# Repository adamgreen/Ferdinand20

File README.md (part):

<br>
Tracking the build of my robot to compete in the
[Seattle Robotics Society's Robo-Magellan](https://robothon.org/rules-robo-magellan/) competition that was to be held on October 3rd, 2020 at the Seattle Center but is now cancelled due to COVID-19. Development of this robot will continue in hopes that it can compete in the future.

## Points of Interest
[SRS Robo-Magellan rules](https://robothon.org/rules-robo-magellan/) <br>
[Notes about our 2014 bot](https://github.com/adamgreen/Ferdinand14#readme) <br>
[Notes from my stalled 2016 attempt](https://github.com/adamgreen/Ferdinand16#readme) <br>
[How to Clone GitHub Repository](#clone-this-repo-and-its-submodules) <br>
[Sawppy the Rover Build Instructions](https://github.com/Roger-random/Sawppy_Rover#readme) <br>

---
## June 27th, 2021
### I2C? What I2C?
The next task I set myself upon was wiring the IMU into the LPC1768 on my Sawppy bot so that I could use it with the [dead reckoning code that I wrote for the Ferdinand16 project](https://github.com/adamgreen/Ferdinand16/tree/master/firmware/robot). When I was working with the IMU hardware back in April, I had it connected to a dedicated LPC1768 on a breadboard and not the one already wired up to my bot. When I went to move it over to the LPC1768 microcontroller on the Sawppy bot, I hit a snag. All of the I2C capable pins on the microcontroller were already being used for their UART functionality: LX-16A servos/motors, MRI debug monitor, and PDB communication.

### Bridge It
In the future, I plan to create my own PCB for the LPC1768 based brains of my bot which will give me access to more pins of the microcontroller. In the meantime, I would like to continue prototyping with the mbed based board that I already have. How can I work around the lack of free I2C pins? It turns out that I still have one set of SPI pins available. Using another microcontroller, I could create a bridge device that reads the IMU sensors via I2C and then sends the resulting readings to my main microcontroller over SPI.

#### LPC1768 as SPI Slave
My first attempt at building this bridge was to use another mbed LPC1768 microcontroller as a SPI slave. When I originally skimmed the mbed SPISlave class documentation I was kind of confused on how to really use it. I then read the LPC1768 User Manual and was even more confused. I tried for several days to get the LPC1768 to reliably send data back to the SPI master but ended up throwing in the towel. I just don't think the SPI peripheral on the LPC1768 hardware is designed properly for use in slave mode:
* There is no way to get an interrupt when the master sends a single byte request. It will only interrupt when the Rx buffer overflows, the Rx FIFO is half full, or 4 byte times have elapsed since the last received byte.
* It is really hard to queue up the Tx data at the right time and if you don't have it queued in time because your code is busy doing something else, the peripheral just takes the oldest already sent data from the Tx buffer and sends it instead.

In the end, I gave up on the LPC1768 and decided to research using another microcontroller from my stash.

#### nRF5x as SPI Slave
I had an [Adafruit Feather nRF52 Pro with myNewt Bootloader - nRF52832](https://www.adafruit.com/product/3574) in my stash of development boards so I pulled up its SPI slave documentation. What I saw there looked very promising:
* You can specify what data should be returned when you have no active data queued up to be sent back.
* Once you do have data to be sent, you queue it all up at once with the help of EasyDMA.

I ported my I2C sensor reading code to the nRF52832 and quickly implemented the SPI bridging code. The SPI Slave functionality on this device worked exactly as expected and I soon had a functional bridge setup between the bot's main LPC1768 and the nRF52 bridge.

Now to get it all installed back on my bot and start writing some dead reckoning code :)

---
## June 4th, 2021
### LX-16A Encoders
 <br>

The [LX-16A servos](https://www.hiwonder.hk/collections/servo/products/hiwonder-lx-16a-serial-bus-servo) used in the [Sawppy Rover](https://github.com/Roger-random/Sawppy_Rover#readme) design have a potentiometer that can be used for reading out the current angle but it can't accurately read all 360 degrees of the rotation. It returns accurate readings between -40 and 280 degrees (320 degrees of rotation) but not such accurate readings for the other 40 degrees of rotation. There are 2 types of inaccurate readings that it returns when in the range between 280 and -40 degrees (the deadzone):
* It will return angle values that fall between 280 and -40 as expected but they aren't accurate. This is the most common case and is easy for me to detect in code. I suspect that there is a carbon arc for the section where it returns correct values (-40 to 280 degrees) and maybe just copper at the two extremes where it returns these incorrect readings. The following diagrams show what I think the internals of the potentiometer look like and where the wiper is located for a few key angles:
  * 280 degrees: This is the maximum valid angle. The potentiometer wiper is contacting the carbon resistive track. <br>
  * -40 degrees: This is the minimum valid angle and shows the potentiometer wiper at the other end of the carbon resistive track. <br> 
  * -50 degrees: This is an angle in the deadzone. The potentiometer is no longer on the carbon resistive track but is also not floating. This explains why the readings back from the LX-16A servo tend to fall around -40 or 280 when in the deadzone since this area of the track is at either the maximum or minimum voltage level since there is so little resistance to the end taps. <br> 
* It will return random angle readings that can fall anywhere in the 360 degree range. I suspect that this happens when the potentiometer wiper is left floating in a gap that must exist between the two ends of the potentiometer to stop the wiper from creating a short between the high and low voltages applied to the opposite ends of the potentiometer. This isn't a common case and is hard to detect in code but we do know that it happens when previous readings place it in the deadzone and the wiper shouldn't dwell in this area for long at the velocities and sampling times that will be used for controlling my robot's motion. <br> 

I tried two methods to work around these inaccurate readings and I will give an overview of them below.

#### Kalman Approach
 <br>
As the old saying goes, "When all you have is a hammer, everything looks like a nail." In my case, my hammer of choice has become the Kalman filter. So my first thought to solve the LX-16A servo encoder problem was to apply a Kalman filter to calculate the current rotational position and velocity. To this end, I started out by re-reading my ["Kalman Filter for Beginners with MATLAB Examples" by Phil Kim](https://www.amazon.com/Kalman-Filter-Beginners-MATLAB-Examples/dp/1463648359). I really like this book. The content is very good. The only down point is the Korean to English translation could use quite a bit of improvement. Once I finished the reread, I wrote up some code to experiment with the Kalman filter which can be seen in the following [commit](https://github.com/adamgreen/Ferdinand20/commit/b95c3b9d9873d6a039cecfaa98e94790804dd103). I played with this code for a few days but I never got the error estimates to a point where the rotational velocity estimate wasn't overly filtered with a lagging response to real world velocity changes. Based on these results, I decided to try another approach which can be best described as a bunch of conditional hacks.

#### Conditional Hacks
The key observation that I take advantage of in my set of hacks is the following:
* If the angle returned from the LX-16A servo is between -40 and 280 degrees, then most likely it is within +/-0.24 degrees (1 lsb) of the actual real world position.

This means that my code treats such position measurements as the truth and uses them to estimate the velocity. There is one exception to this and I will discuss it more later.

The second observation is very much related to that first one:
* If the angle returned from the LX-16A servo is instead between 280 degrees and -40 degrees then it is in a deadzone where the returned values are much less accurate.

When my code detects that the returned position readings are in this deadzone, it uses the previous position and velocity estimates and sampling time to calculate new position estimates by assuming constant velocity between the samples.

The handling of those two angle ranges gets us most of the way to a solution but I needed to add a few more conditional hacks to produce a functional filter:
* When the wiper is in the middle of the deadzone, it will be floating and returning completely random values that fall in or outside of the deadzone. I have the code ignore the first non-deadzone sample when the previous sample was from the deadzone. If this ignored non-deadzone angle is followed by another then the code transitions into the non-deadzone logic previously described. This does mean that the first good angle reading is always dropped when transitioning out of the deadzone but that is a small price to pay for filtering out these completely erroneous readings. I only expect a single erroneous reading caused by a floating wiper when the rover is moving since there should be a very low likelihood that the wiper stays in this region for multiple samples as the motor is rotating.
* Don't update the velocity until it has two or more non-deadzone position readings. The last interpolated position from the deadzone logic might be so incorrect that it would result in a very bad estimate of the velocity.
* Use an exponential recursive moving average filter to smooth out the velocity calculations. We don't want high frequency noise in this calculation to later impact the PID control loop.

```c++
void LX16A_DriveMotor::updateState()
{
    // Calculate time since last running of the filter and grab the current servo position in close temporal
    // relation to the time capture.
    int16_t servoPos = m_servo.getPosition();
    uint32_t currSampleTime = m_timer.read_us();
    uint32_t elapsedMicroSec = currSampleTime - m_lastSampleTime;
    m_lastSampleTime = currSampleTime;
    float dt = (float)elapsedMicroSec / 1000000.0f;

    EncoderState prevState = m_currState;
    if (ignoringNonDeadZoneSamples(servoPos) || isServoInDeadZone(servoPos))
    {
        // The servo position could be off by as much as +/-20 degrees when in dead zone of the pot.
        // Assume that the motor is still spinning at the same rate when in dead zone.
        m_currState.angle = constrainAngle(prevState.angle + prevState.velocity * dt);
        m_currState.velocity = prevState.velocity;
        m_wasInDeadZone = true;
        printf("*");
    }
    else
    {
        // The pot reading should be accurate so use it.
        m_currState.angle = constrainAngle(servoPos * LX16A_SERVO_TO_RADIAN_VALUE);

        if (m_wasInDeadZone)
        {
            // Don't want to base current velocity off of previously interpolated position.
            m_currState.velocity = prevState.velocity;
        }
        else
        {
            // Calculate velocity from change in angle and then use weighted average so that it doesn't snap too much.
            const float weight = VELOCITY_AVERAGING_WEIGHT;
            float angleDelta = constrainAngle(fmodf(m_currState.angle - prevState.angle, 2.0f*(float)M_PI));
            float velocity = angleDelta / dt;
            m_currState.velocity = (1.0f-weight)*m_currState.velocity + weight*velocity;
        }
        m_wasInDeadZone = false;
    }

    updatePID(dt);
}
```

I may have to add code in the future to handle the motor being stopped when in the deadzone or even worse, stopped right at the point where the potentiometer wiper is left floating. I will cross this bridge once I encounter it so that I have scenarios to use for testing my attempts to resolve it.

### Closing the Loop
Once I had a way to obtain a reasonably reliable estimate of the servo's rotational velocity, I pulled over my PID code from my old [Ferdinand16 repository](https://github.com/adamgreen/Ferdinand16#readme). The biggest changes I made to this code after copying include:
* Now allowing the sample time to be changed between PID updates as the frequency of the LX-16A servo position reads may not be as consistent as my previous uses of the PID control algorithm.
* Ferdinand16 required the angle error to be normalized between +/- 180 degrees and the PID code had this hardcoded into it. I updated the code to take an optional callback for performing such normalizations when required. It isn't required for LX-16A motor velocity control.

Now that I had a way to close the loop on the control of the motor velocities, I went into the existing ```SawppyDrive``` class and plugged in my new ```LX16A_DriveMotor``` class for controlling the 6 servos that spin the wheels (while leaving the 4 turning servos as is). Once this switch had been made, I could drive my Sawppy bot around by remote control as before but now the wheel velocities were running under closed loop control.

### MRIPROG / BLEMRI Issues with new macOS and MRI Updates
When I started testing the new PID code on my actual Sawppy based robot, I hit a few issues with my Bluetooth Low Energy (BLE) programming/debugging tools that I had to address first. It turns out that it needed updates to work with the newer version of my [MRI debug monitor](https://github.com/adamgreen/mri#readme), my new MacBook Air, and Big Sur updates:
* I updated **mriprog** to move the entry point for the LPC1768 bootloader into entry.S so that I can use assembly language code to initialize the stack pointers (MSP & PSP) to the desired value since the current MRI doesn't allow for modifying the stack pointers from GDB. Once the stack pointers are set, it just branches to the original main() code.
* MRI now contains 6 more special registers in the context (MSP, PSP, PRIMASK, BASEPRI, FAULTMASK, CONTROL). I updated **mriprog**'s gdbRemote module to take these into account.
* When my new laptop communicates with the nRF51 BLE to UART bridge, it tends to corrupt a few packets that need to be resent. I made a few updates to **mriprog** to better handle these resends:
  * Instead of reporting each packet error encountered, just count them and report the number of retries at the end along with the other statistics.
  * Reduce PACKET_MAX_DATA from 16k to 4k so that if the CRC fails on a packet then less data needs to be resent.
* I updated my **blemri** code to handle a BLE change introduced with Big Sur. Once the Mac has been connected to a BLE device such as BLEMRI, Big Sur only returns the information that it cached on the first connection and this doesn't include the 128-bit service UUID from the scan response. My code used this UUID for filtering when performing BLE device discovery. I modified the firmware to no longer advertise the unique service UUID and now just advertise the Nordic UART service UUID actually supported by the device as it is no longer of use for filtering. I now have the application running on macOS perform BLE discovery with no filtering and then check the local device name on each discovered device, looking for ones named BLEMRI.
* I increased the minimum and maximum connection interval from 7.5ms to 15ms in my BLEMRI firmware to meet the Apple design recommendations. My iPhone is now able to stay connected for over 100 seconds. My iPhone would previously drop the connection when it couldn't agree with the device on connection parameters. This change doesn't decrease the throughput that much as BLE allows multiple packets to be scheduled per interval. It would increase the turn around time to get the response back from commands. The throughput is still above 5kB/s after this change so I will keep it.
* I copied the **mriprog** utility from my [older BB-8 project](https://github.com/adamgreen/bb-8/tree/master/mriprog) and placed it in its [own repository](https://github.com/adamgreen/mriprog) so that it could be included as a submodule in this Ferdinand20 repository.

### Next Steps
* ~~Debug and fix some of the issues that I encountered while performing the latest testing on my Sawppy control code.~~
* Wire the IMU into the LPC1768 on my Sawppy bot.
* Port my [heading maintaining code from my Ferdinand16 project](https://github.com/adamgreen/Ferdinand16/tree/master/firmware/robot) and get it working on this bot.

---
## April 23rd, 2021
### New IMU Hardware - Up and Running!
<br>
I spent this week getting the [Adafruit Precision NXP 9-DoF Breakout Board](https://www.adafruit.com/product/3463) working with my existing [Ferdinand16](https://github.com/adamgreen/Ferdinand16#readme) IMU code:
* I copied over the Kalman filter and I2C drivers and got them working in a newer build environment:
  * I updated my FlashFileSystem driver to work with the newer build of the mbed SDK. This file system is used to read the ```config.ini``` embedded in the firmware image as part of the build process.
  * I reorganized the code to move the drivers out into a ```libs/``` folder so that they didn't clutter up the ```software/``` folder.
* I rewrote the I2C drivers to work with the NXP FXOS8700CQ Accelerometer/Magnetometer and the NXP FXAS21002C Gyroscope:
  * My original IMU code only ran at 100Hz. I added the ability to switch between sampling rates (100/200/400Hz) from a setting in ```files/config.ini```. I am now using 200Hz for testing as 400Hz swamps the UART with too much data when communicating the orientation back to the PC in certain scenarios. It could probably run at 400Hz on the robot though as it doesn't require this communication.
  * Now samples the FXOS8700CQ Accelerometer/Magnetometer measurements on a data ready interrupt rather than a fixed timer. According to an errata from NXP, this is supposed to decrease the chance of I2C communications interfering with the magnetometer analog front end.
* I copied over my [Ferdinand14 calibration application](https://github.com/adamgreen/Ferdinand14/tree/master/calibration) and it pretty much just worked with the latest release of Processing.
* I was then able to use the calibration application to [calculate the settings for these sensors](https://github.com/adamgreen/Ferdinand14#august-19-2014) and update them in ```files/config.ini```.
* I copied over my [Ferdinand16 orientation application](https://github.com/adamgreen/Ferdinand16/tree/master/processing/orientation) and got it working on newer builds of [Processing](https://processing.org):
  * I had to use the Processing 4 alpha as the 3D graphics are broken in the current Processing 3 release on macOS.
  * I fixed some bugs that I noticed when testing my new sensor that I must have missed in previous testing 5 years ago.
  * I updated it to pull more configuration options from the ```config.ini``` rather than being hardcoded (variance settings, sampling rate, etc) in the sources. It also now reads from the same ```files/config.ini``` built into the firmware so that they use matching configuration options.
  * This program is used to measure the gyro and accelerometer/magnetometer variances to be placed in ```config.ini```. If the sensor is left unmoved for a few minutes, the statistics of how each sensor contributes to noise in the quaternion representation of the orientation will be dumped to the Processing console.

Issues I encountered while testing this port:
* The temperature readings on the NXP FXAS21002C Gyroscope  are lower resolution than the InvenSense ITG-3200 Gyroscope that I used before. This limits the resolution of the gyro drift compensation that I can use on this sensor. The good news is that this gyro shows significantly less drift during my testing at temperatures between 20 and 30C.
* While the gyro drift was pretty low when the die temperature was between 20 and 30C, it showed some very odd non-linear drift characteristics at lower temperatures which would be difficult to calibrate away. Luckily my bot isn't likely to be running at lower temperatures and the drift appears to be linear above 20C so my existing drift compensation can still be used to further reduce the drift.

* The NXP FXAS21002C Gyroscope measurements contain more noise than I encountered with the InvenSense ITG-3200 Gyroscope. The noise resulted in a 10x increase in the ```compass.gyro.variance``` setting.
```diff
-compass.initial.variance=1.0E-4
-compass.gyro.variance=6.5E-11
-compass.accelerometer.magnetometer.variance=1.0E-5
+compass.initial.variance=2.0E-4
+compass.gyro.variance=6.0E-10
+compass.accelerometer.magnetometer.variance=2.0E-4
```
* I see a lot more jitter in the orientation when run in Accelerometer/Magnetometer only mode. This jitter can also be seen in the Kalman filtered results, though much reduced as one would expect. If I hardcode the magnetometer reading and only use the accelerometer, there is almost no jitter at all so it is the magnetometer that causes it. Actually I think the accelerometer in the NXP FXOS8700CQ is better than the one I used previously.

### What's Inside the Box?
What's inside the brown box shown in the animated GIF at the beginning of this post?
<br><br>
It contains a [mbed 1768](https://os.mbed.com/platforms/mbed-LPC1768/) connected to a [Adafruit Precision NXP 9-DOF Breakout Board](https://www.adafruit.com/product/3463).

### Next Steps
Now that I have my IMU code working again on newer hardware, I want to continue fleshing out the dead reckoning part of the project. With that in mind, I will concentrate on the following next week:
* ~~Determine distance travelled by the wheels on my [Sawppy](https://github.com/Roger-random/Sawppy_Rover#readme) frame.~~

---
## April 16th, 2021
### Upgrade my IMU Hardware?
#### Sparkfun 9 DoF - Sensor Stick
</br>
Back in 2014, I decided to use the [Sparkfun 9 DoF - Sensor Stick](https://www.sparkfun.com/products/retired/10724) as the accelerometer, magnetometer, and gyroscope for our [Ferdinand14 project](https://github.com/adamgreen/Ferdinand14#readme).

#### Adafruit Precision NXP 9-DOF Breakout Board
</br>
When starting out on Ferdinand20, I noticed that Sparkfun no longer sells this board. This was a good reason to look around at new sensors as I suspected there would now be even more precise units on the market. This research led me to the [Adafruit Precision NXP 9-DOF Breakout Board](https://www.adafruit.com/product/3463) which appears to offer more precision in all axis. I ordered one of these new IMU boards from Adafruit back in July of 2019. This way I would have it if I decided to make the leap and update my Kalman filter to work with a more current sensor package. I spent time this week evaluating whether I should make that leap:
* I code reviewed my existing [Kalman filter and I2C drivers](https://github.com/adamgreen/Ferdinand16/tree/master/libs/Sparkfun9DoFSensorStick). From looking at this code, it seems that the only work that would need to be completed to make the switch would be updating the I2C drivers to work with the newer NXP sensors, run a calibration pass, and update the config.ini with the new calibration data. Nothing else was specific to the sensors in use.
* I read the datasheets for the NXP FXOS8700CQ Accelerometer/Magnetometer and the NXP FXAS21002C Gyroscope to learn how difficult it would be to update the I2C drivers. From what I read in those datasheets, it should only take a part of a day to make those updates. They are pretty simple and the FXOS8700CQ datasheet even includes sample C code. I also noticed that these sensors look like they all have more precision than my current IMU hardware and can run at a higher sample rate (400Hz vs 100Hz). The only thing less precise is the temperature readings on the gyroscope which might have an impact on my drift corrections.

### Next Steps
Based on my recent research, I think it should only take a week or two to switch to this new IMU hardware:
* ~~I need to update the I2C drivers for the two chips on this new breakout board.~~
* ~~Run the resulting raw sensor readings through my [existing calibration process](https://github.com/adamgreen/Ferdinand14#august-19-2014) to create an updated config.ini.~~
* ~~Test the new hardware with my [existing Processing based GUI](https://github.com/adamgreen/Ferdinand16/tree/master/processing/orientation).~~

---
## April 11th, 2021

Last year I updated the Power Distribution Board enclosure to use a round push button switch for the Manual/Auto mode selection but I only had a green version of the switch on hand. I now have a [red version of the switch](https://www.adafruit.com/product/916) that I could install instead.

---
## April 9th, 2021
### BLE Remote Experiments

The BLE connection between the power distribution board (PDB) and the remote control that I built last year isn't as reliable as my initial prototypes. I conducted a few experiments this week to help narrow down what might be the cause. These experiments included:
* Running my PDB code on a micro:bit again like I did in the initial prototype. This did seem to work a bit better than the PDB hardware in my actual robot but not significantly better. I think the fact that I didn't initially have the logic to shutoff the relay after missing ```MAX_MISSED_BLE_PACKETS``` packets from the remote is the main reason I didn't see the problem on the earlier prototype.
* I tried moving the relay in relation to the BLE antenna. It didn't seem to have a noticeable impact. I could even place the relay right over the antenna and it didn't become any less reliable.
* If I placed a low resistance load across the relay outputs to allow a largish current (~5A) to flow, that seemed to cause more problems for the BLE connection. Especially if placed too close to the antenna.
* I tried switching to an [Adafruit Feather nRF52 Bluefruit LE - nRF52832](https://www.adafruit.com/product/3406) with its chip antenna. It actually performed worse than the micro:bit setup with its PCB antenna.
* I found that holding the remote control so that its PCB was in the vertical orientation resulted in some of the best increases in reliability, even with the PDB mounted in the actual robot.

### Lessons Learned:
* Keep high current traces on PDB away from the BLE antenna.
* Have antenna on BLE modules protruding out over the PCB if possible.
* Mount BLE PCB antenna in vertical orientation.
* For PDB, place it at top so there isn't much between it and the remote control.
* For remote, try to place it so that my hand won't be between the two antenna.

---
## March 29th, 2021
### Cone Detection?
The computer vision unit of the [RoboGrok course](http://www.robogrok.com) showed a way to highlight red objects by subtracting the green and blue channel values from the red channel value so that only pixels with red and no blue and/or green component would show up brighter. The following two screen captures show what a traffic cone and a Robothon 2015 t-shirt look like when viewed with this red-only pixel filter applied. The left window in each screen capture shows the full RGB of the scene and the right window shows the same scene with the red-only filter applied.
#### Normal Indoor Lighting

#### Reduced Indoor Lighting

Some key takeaways from this experiment:
* In both lighting situations, the traffic cone always shows up as one of the brightest things in the red-only image. When testing inside, I never really got any false negatives where the cone wouldn't show up as one of the brightest objects in the red-only image.
* There are false positives, as we can see that the orange Robothon t-shirt shows up quite bright as well.
* Running connected components on the red-only image could segment the image into separate bright red/orange objects like the traffic cone and t-shirt.
* Additional object recognition algorithms would need to be run on each of the segmented objects to remove the false positives and only identify the traffic cones of interest.
* During previous outdoor testing I noticed that traffic cones show up as bright white when all color channels are saturated by the bright sunlight. I need to perform more outdoor testing to see if I need to add a physical filter such as [this one](https://openmv.io/collections/products/products/polarizing-filter).

### Future Computer Vision Work
I have decided not to continue with this experimentation on my MacBook Air any further as I plan to use the [OpenMV camera](https://openmv.io) on the actual robot and it makes more sense to continue future experimentation with that device instead.

When I get back to looking at cone detection, I should probably first address these work items:
* Code review the OpenMV code base and see how it is implemented incase I want to modify some of the low level C/C++ code instead of just using the Python layer.
* Can I attach the OpenMV camera to my robot, drive it around, and record video footage? This would be useful for future playback and testing while I develop/refine the cone detection algorithm.
* Do some internet searching to see if anyone else has already come up with a robust cone detector using the OpenMV camera.

---
## March 23rd, 2021
### Starting Back Up
I paused this project for a few months to get some work done on other projects:
* [Halloween foam pumpkin with dragon eyes](https://github.com/adamgreen/DragonEyes).
* Updated my [NeoPixel Christmas tree](https://github.com/adamgreen/NeoPixelTree) to use a more robust 3D printed frame with a pre-made string of lights.
* Learned more about OpenSCAD by designing a few things that I needed around the house.
* I completed the [RoboGrok online robotics courses](http://www.robogrok.com), Robotics 1 and Robotics 2. While some of the material in the course is applicable to mobile robots like this one, it concentrated more on industrial type of applications (ie. robotic arms).

### Next Steps
* ~~The [RoboGrok course](http://www.robogrok.com) had some interesting sections on computer vision. I would like to take some of my vision coursework and try modifying it to detect traffic cones for the [Robo-Magellan](https://robothon.org/rules-robo-magellan/) competition.~~
* ~~The BLE connection between the power distribution board and the remote control that I built for the bot last year isn't as reliable as my initial prototypes. I want to do some experiments to determine what the actual cause is so that I can redesign it in the future.~~
* ~~Figure out how I want to progress on the IMU front by picking one of the following approaches:~~
  * ~~Hack up a connection to the IMU that I built for my earlier [Ferdinand16](https://github.com/adamgreen/Ferdinand16) attempt.~~
  * ~~Port the Ferdinand16 firmware to work with the [NXP 9-DoF Breakout Board - FXOS8700 + FXAS21002](https://www.adafruit.com/product/3463) IMU board that I bought from Adafruit when I started working on Ferdinand20.~~

---
## October 19th, 2020
### Project on Pause
If the 2020 running of the SRS Robo-Magellan competition hadn't been cancelled this year, it would have been run a couple of weekends ago. I wouldn't have had enough ready to actually compete this year though. I haven't even started on the main robot control electronics yet. Before I finalize the PDB design and start working on those main control electronics, I want to take a break and work on some other foolish electronic projects. Hopefully I can get back to this project before the end of the year and get it ready for next year's competition.

---
## September 27th, 2020
I have completed the updates to the PDB enclosure to make it smaller and look less out of place on the back of the Sawppy rover.

### Old PDB Enclosure

### New PDB Enclosure

I made it smaller by dropping the large covered toggle switch for the manual/auto mode selection and instead used the same model as the power switch. I am currently using a green lit one since that is what I had on hand but I will probably purchase a red one and use it in the future instead. I also rotated the PCB by 90° which helped reduce the height of the enclosure. The OpenSCAD design was modified to take the dimensions of the PCB, switches, and label text to automatically calculate the smallest possible enclosure size.

Once I had the size reduced, I added a top and removable back panel to hide the internal electronics and make it a bit more tolerant of wet outdoor conditions.

---
## September 14th, 2020
I completed the first functional prototype of the remote control enclosure last weekend.

I still have tweaking that I want to do on its 3D design. Before I do that though, I will probably switch back to the 3D design of the Power Distribution Board Panel and apply some tweaks that I have been thinking about since I mounted the last one on my bot.

---
## August 27th, 2020
I am still cranking away at OpenSCAD, working on the enclosure for the remote control. I have been iterating on the design of the button used to depress the deadman switch so I have just been printing that portion of the remote control top to speed things up:<br>

I will be taking a break from this project for a few days while I work on another project. Once I am done with that, I will start working on the handle for the remote control.

---
## August 21st, 2020
I have been busy with OpenSCAD this week, trying to turn my previous remote control mockup into a functional enclosure. I still have quite a bit more work to do before I complete it but I thought I would share some photos of my current progress:<br>
* I designed a mockup of the PCB with joystick installed to digitally place in the enclosure and check for fit.<br>

* I now have everything in the top portion of the remote control completed except for the button to activate the deadman switch.<br>

---
## August 16th, 2020
### 3D Printed PDB Panel

This weekend I finished the OpenSCAD design for the PDB enclosure and got it mounted on the Sawppy frame. It works but there are some things I might improve in the future:
* It is a little larger than I would like. It doesn't really fit in with the scale of the Sawppy rover itself.
* The switch labels are a bit hard to read. I should use a more legible (fatter & simpler) font. Switching to one layer of white filament for the layer that bridges behind the text does make it pop though so I will continue to do that in the future.
* Tilt the screen up to make it easier to view when standing behind it.

I demoed my rover at today's online [Vancouver Robotics Club meetup](https://www.meetup.com/VancouverRoboticsClub). It was nice to have made enough progress on it to have something that I could actually demo.

### SRS Robothon 2020 Cancelled
Donna Smith was at today's meetup and announced that [Robothon will be cancelled for 2020](https://robothon.org/2020/05/18/announcing-robothon-20202/). I now have another year to get this rover ready for competition.

### Next Steps
* ~~Start working on the OpenSCAD design of the enclosure for the remote control based on my existing prototype.~~

---
## August 12th, 2020
### PDB Installed - Kind Of
<br>
Since I haven't designed the panel for the PDB yet, I used elastic bands to mount the PDB to the Sawppy frame for now. Hacky but it worked! Once the PDB was temporarily mounted I was able to update the SawwpyDrive test code to make use of the PdbSerial driver to drive the rover around using the remote control.

When I first started using the remote control with Sawppy I noticed that the motor power relay would click on and off as I moved around the robot. I ended up increasing the **MAX_MISSED_BLE_PACKETS** define in the PDB firmware to allow up to 30 missed packets before flagging the remote as disconnected.

### Next Steps
* ~~Start working on the OpenSCAD design of the panel to be mounted on Sawppy to contain the PDB electronics.~~

---
## August 11th, 2020
### Feature Complete
I now consider the firmware for the [Power Distribution Board](software/PDB) and [Remote Control](software/RemoteControl) units to be feature complete. I have also implemented the [PdbSerial driver](software/PdbSerial) to make it easier for the robot microcontroller to interact with the PDB. The inbound auto/manual packets from the PDB are processed in the UART ISR as the bytes arrive and the outbound informational text to the PDB are sent in the background using DMA.

### Next Steps
* ~~Connect the motor power outputs from the PDB to the LPC1768 robot microcontroller board.~~
* ~~Write code for the LPC1768 to let it be driven around via the remote control when the PDB is in manual driving mode.~~
* ~~Start working on the OpenSCAD design of the panel to be mounted on Sawppy to contain the PDB electronics.~~

---
## August 9th, 2020
### Remote Control PCBs
The remote control PCBs arrived from OSHPark earlier this month.
<br><br>
A day after the boards arrived, I soldered them up.
<br>
<br><br>
There are only a few things I would change if I were to respin this board:
* The ground pads didn't have enough thermal relief. The ground plane was pretty large on this board and it really wicked a lot of heat away from the soldering iron.
* The pads on the right angled dead man switch should have been longer to make it easier to make contact with the soldering iron.

Once I had the PCBs soldered up, I updated the firmware to work on them and then got to quickly finalizing the code.

### Remote Control Current Usage
With the remote control code finalized I was to start measuring the remote's current usage in various states:
| BLE State                   | Current |
|-----------------------------|---------|
| Fast Advertising            | 2mA     |
| Normal Advertising          | 1.1mA   |
| Connected & Sending JoyData | 1.5mA   |
| Deep Sleep                  | 20µA    |

The 2xAAA batteries should be able to power the device in deep sleep for quite some time. That means that I don't need to use a power switch on the remote control. I already have it coded to enter deep sleep after 4 minutes of not being connected to the PDB and pressing the dead man switch will wake it up so that it can attempt to reconnect to the PDB.

### Power Distribution Board - More Firmware Improvements
The following photos show the top and bottom of the PDB PCB after I applied bodge wires to work around the mistakes that I made in the original PCB design:
<br><br>
<br>

Over the last week, I have continued to work on the PDB to improve its firmware:
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
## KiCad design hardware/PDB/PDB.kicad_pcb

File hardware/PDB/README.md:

# Bill of Materials
Description | Quantity | Part Number(s)
------------|----------|---------------
[1N4148WT Diode](https://www.digikey.com/product-detail/en/1N4148WT/1N4148WTCT-ND) | 1 | D1
[Dynastream N5 ANT/BLE SoC Module](https://www.digikey.com/product-detail/en/N5150M5CD/1094-1021-ND) | 1 | U3
[MIC5205 Linear Regulator - 3.3V 150mA SOT23-5](https://www.digikey.com/products/en?keywords=576-1259-1-ND) | 1 | U1
[L4931ABD50-TR Linear Regulator - 5V 250mA](https://www.digikey.com/product-detail/en/L4931ABD50-TR/497-1156-1-ND) | 1 | U2
[MMBT2222ALT3G NPN Transistor](https://www.digikey.com/product-detail/en/MMBT2222ALT3G/MMBT2222ALT3GOSCT-ND) | 1 | Q1
[SMAJ4739A-TP Zener Diode](https://www.digikey.com/product-detail/en/SMAJ4739A-TP/SMAJ4739A-TPCT-ND) | 1 | D2
[0.1uF Capacitor](https://www.adafruit.com/product/441) | 1 | C1
[470pF Capacitor](https://www.digikey.com/product-detail/en/CC0805KRX7R9BB471/311-1124-1-ND) | 1 | C2
[1uF Capacitor](https://www.adafruit.com/product/441) | 4 | C3, C4, C5, C6
[680 ohm Resistor](https://www.adafruit.com/product/441) | 1 | R1
[1k ohm Resistor](https://www.adafruit.com/product/441) | 2 | R2, R3
[Fuse Holder 20A Circuit Blade Surface Mount](https://www.digikey.com/product-detail/en/3587TR/36-3587CT-ND) | 3 | F1, F2, F3
[Female Header for LCD 1x12 - 0.1" Through-Hole](https://www.digikey.com/product-detail/en/chip-quik-inc/HDR100IMP40F-G-V-TH/HDR100IMP40F-G-V-TH-ND) | 1 | J2
[Molex_SPOX_5267-04A_1x04_P2.50mm_Vertica](https://www.digikey.com/product-detail/en/0022035045/WM18888-ND) | 1 | J4
[Molex_SPOX_5267-03A_1x03_P2.50mm_Vertical](https://www.digikey.com/product-detail/en/0022035035/900-0022035035-ND) | 2 | J5, J6
[Sparkfun SPDT-JQX-15F Relay](https://www.sparkfun.com/products/10924) | 1 | K1
[Adafruit 1.54" 240x240 Wide Angle TFT LCD Display](https://www.adafruit.com/product/3787) | 1 | J2
[Metal Pushbutton - Latching (16mm, Green)](https://www.sparkfun.com/products/11973) | 1 | J5
[Toggle Switch and Cover - Illuminated (Red)](https://www.sparkfun.com/products/11310) | 1 | J6
[XT60 Connectors - Male/Female Pair](https://www.sparkfun.com/products/10474) | 1 | J1
[Deans Connectors - Male/Female Pair](https://www.digikey.com/product-detail/en/PRT-11864/1568-1659-ND) | 1 | J3

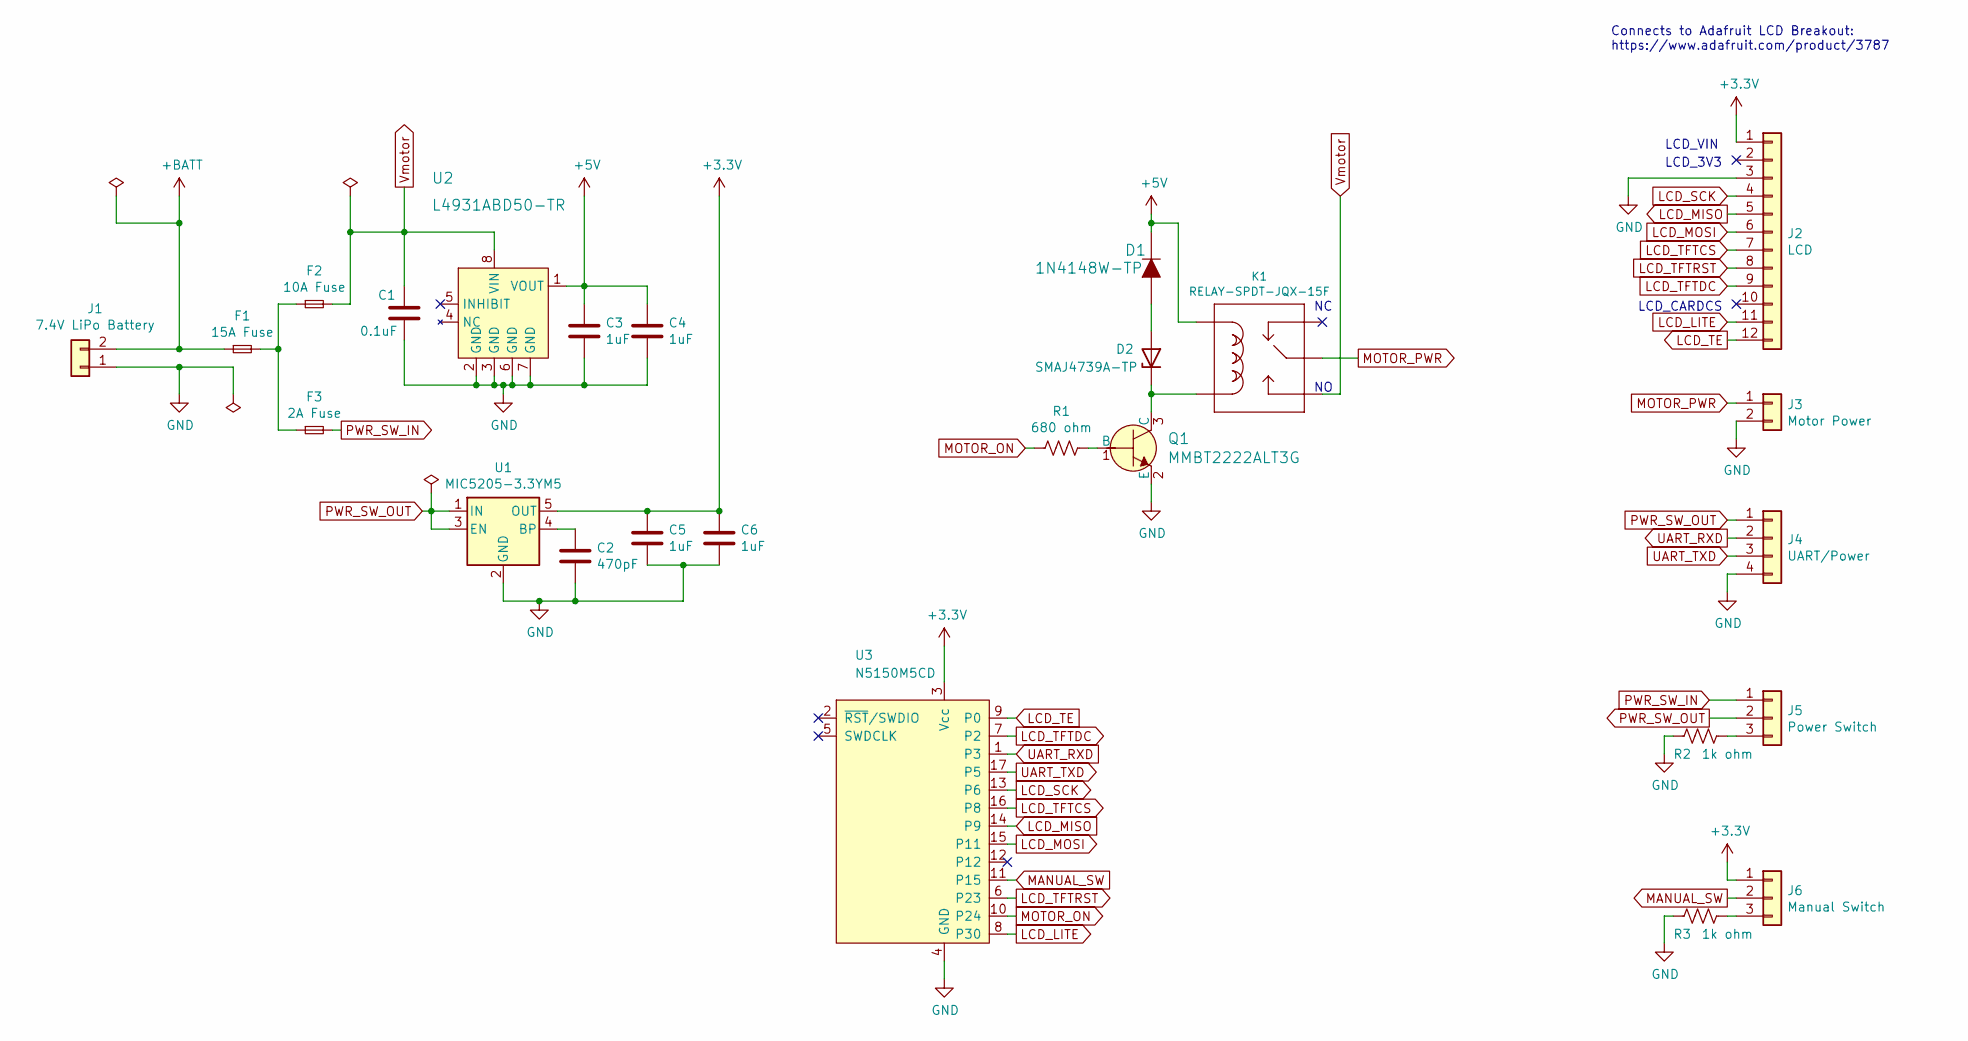
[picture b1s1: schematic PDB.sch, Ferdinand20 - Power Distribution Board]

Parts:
C1: 0.1uF; C_0805_2012Metric
C2: 470pF; C_0805_2012Metric
C3, C4, C5, C6: 1uF; C_0805_2012Metric
D1: 1N4148W-TP; SOD-123; MPN 1N4148W-TP; Digi-Key_PN 1N4148WTPMSCT-ND
D2: SMAJ4739A-TP; D_SMA
F1: 15A Fuse; SMD_Keystone_Fuse
F2: 10A Fuse; SMD_Keystone_Fuse
F3: 2A Fuse; SMD_Keystone_Fuse
J1: 7.4V LiPo Battery; TerminalBlock_bornier-2_P5.08mm
J2: LCD; PinHeader_1x12_P2.54mm_Vertical
J3: Motor Power; TerminalBlock_bornier-2_P5.08mm
J4: UART/Power; Molex_SPOX_5267-04A_1x04_P2.50mm_Vertical
J5: Power Switch; Molex_SPOX_5267-03A_1x03_P2.50mm_Vertical
J6: Manual Switch; Molex_SPOX_5267-03A_1x03_P2.50mm_Vertical
K1: RELAY-SPDT-JQX-15F; SparkFun-Electromechanical-RELAY-T90
Q1: MMBT2222ALT3G; SOT-23-3; MPN MMBT2222ALT3G; Digi-Key_PN MMBT2222ALT3GOSCT-ND
R1: 680 ohm; R_0805_2012Metric
R2, R3: 1k ohm; R_0805_2012Metric
U1: MIC5205-3.3YM5; SOT-23-5_HandSoldering
U2: L4931ABD50-TR; SOIC-8_W3.9mm; MPN L4931ABD50-TR; Digi-Key_PN 497-1156-1-ND
U3: N5150M5CD; adam_custom-N5150M4CD_TOP

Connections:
+3V3: C5.1, C6.1, J2.1, J6.1, U1.5 (OUT), U3.3 (Vcc)
+5V: C3.1, C4.1, D1.K, K1.COIL1, U2.1 (VOUT)
+BATT: F1.1, J1.2
GND: C1.2, C2.2, C3.2, C4.2, C5.2, C6.2, J1.1, J2.3, J3.2, J4.4, Q1.2 (E), R2.2, R3.2, U1.2 (GND), U2.2 (GND), U2.3 (GND), U2.6 (GND), U2.7 (GND), U3.4 (GND)
LCD_LITE: J2.11, U3.8 (P30)
LCD_MISO: J2.5, U3.14 (P9)
LCD_MOSI: J2.6, U3.15 (P11)
LCD_SCK: J2.4, U3.13 (P6)
LCD_TE: J2.12, U3.9 (P0)
LCD_TFTCS: J2.7, U3.16 (P8)
LCD_TFTDC: J2.9, U3.7 (P2)
LCD_TFTRST: J2.8, U3.6 (P23)
MANUAL_SW: J6.2, U3.11 (P15)
MOTOR_ON: R1.2, U3.10 (P24)
MOTOR_PWR: J3.1, K1.MAIN
unnamed: C2.1, U1.4 (BP)
unnamed: D1.A, D2.2 (A)
unnamed: D2.1 (K), K1.COIL2, Q1.3 (C)
unnamed: F1.2, F2.1, F3.1
unnamed: J5.3, R2.1
unnamed: J6.3, R3.1
unnamed: Q1.1 (B), R1.1
PWR_SW_IN: F3.2, J5.1
PWR_SW_OUT: J4.1, J5.2, U1.1 (IN), U1.3 (EN)
UART_RXD: J4.2, U3.1 (P3)
UART_TXD: J4.3, U3.17 (P5)
Vmotor: C1.1, F2.2, K1.NO, U2.8 (VIN)

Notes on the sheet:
LCD_CARDCS
LCD_3V3
LCD_VIN
Connects to Adafruit LCD Breakout: https://www.adafruit.com/product/3787

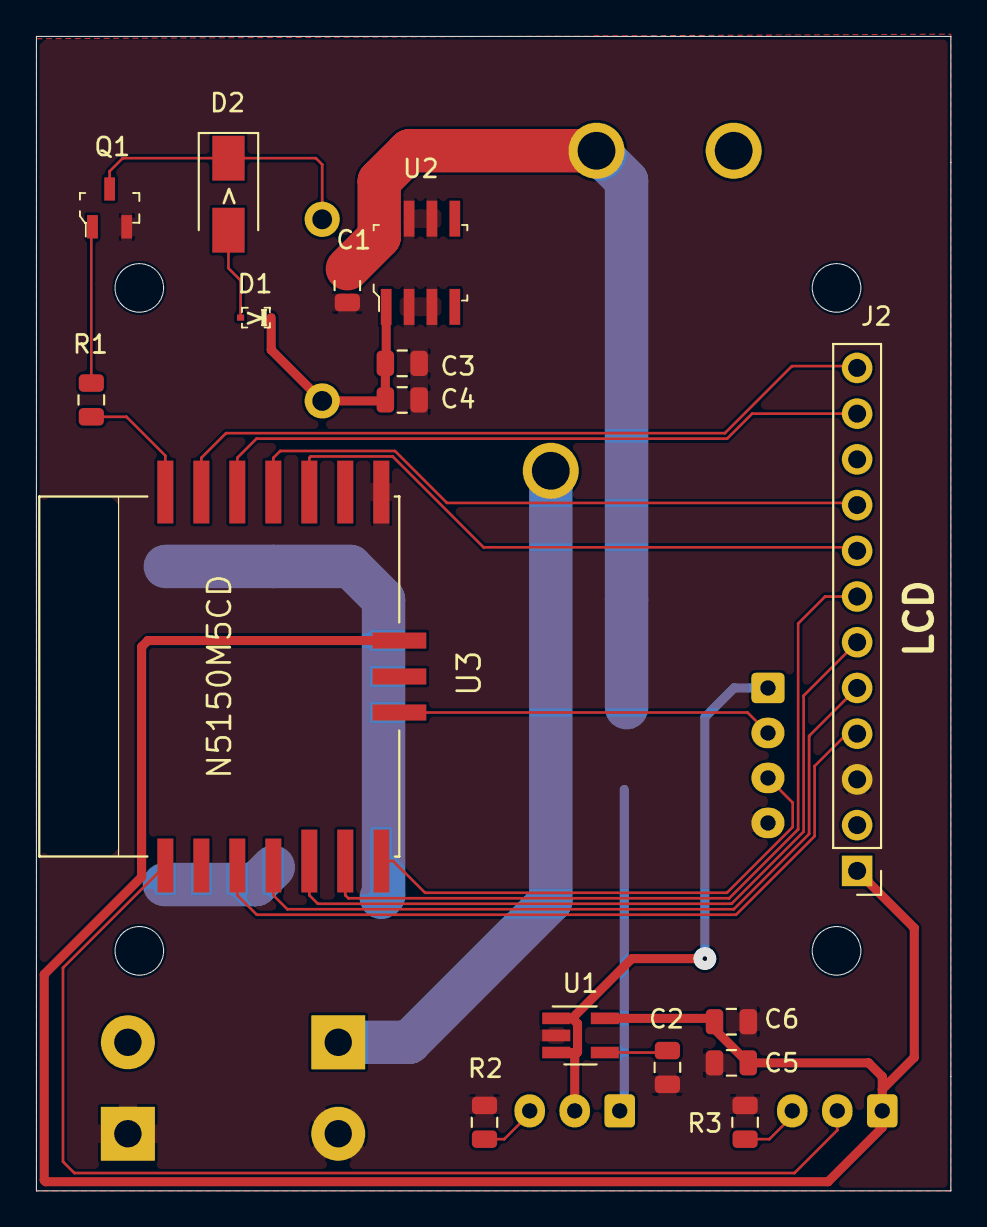
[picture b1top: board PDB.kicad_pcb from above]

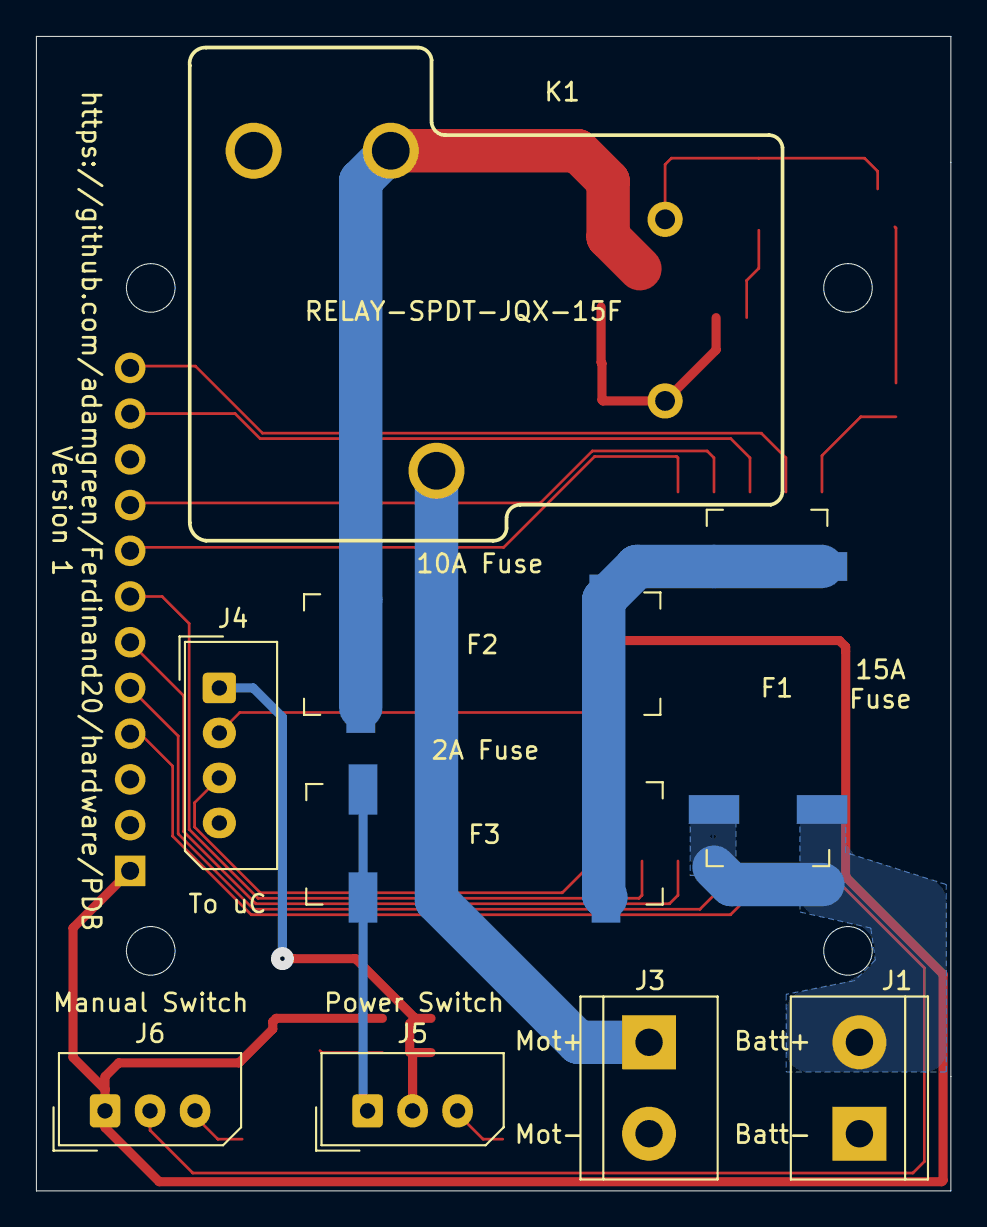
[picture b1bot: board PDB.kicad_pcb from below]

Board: 2 copper layers, 50.8 x 64.1 mm, 25 parts (9 on the bottom side), 27 nets.

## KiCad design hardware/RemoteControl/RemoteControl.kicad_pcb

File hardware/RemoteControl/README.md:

# Bill of Materials
Description | Quantity | Part Number(s)
------------|----------|---------------
[Dynastream N5 ANT/BLE SoC Module](https://www.digikey.com/product-detail/en/N5150M5CD/1094-1021-ND) | 1 | U1
[Tactile Momentary NO Right Angle Switch](https://www.digikey.com/product-detail/en/PTS645VM13SMTR92LFS/CKN10828CT-ND) | 1 | S2
[Thumb Joystick](https://www.sparkfun.com/products/9032) | 1 | S1
[2 x AAA Battery Holder](https://www.digikey.com/product-detail/en/SBH421AS/SBH421AS-ND) | 1 | Batt+ / Batt-

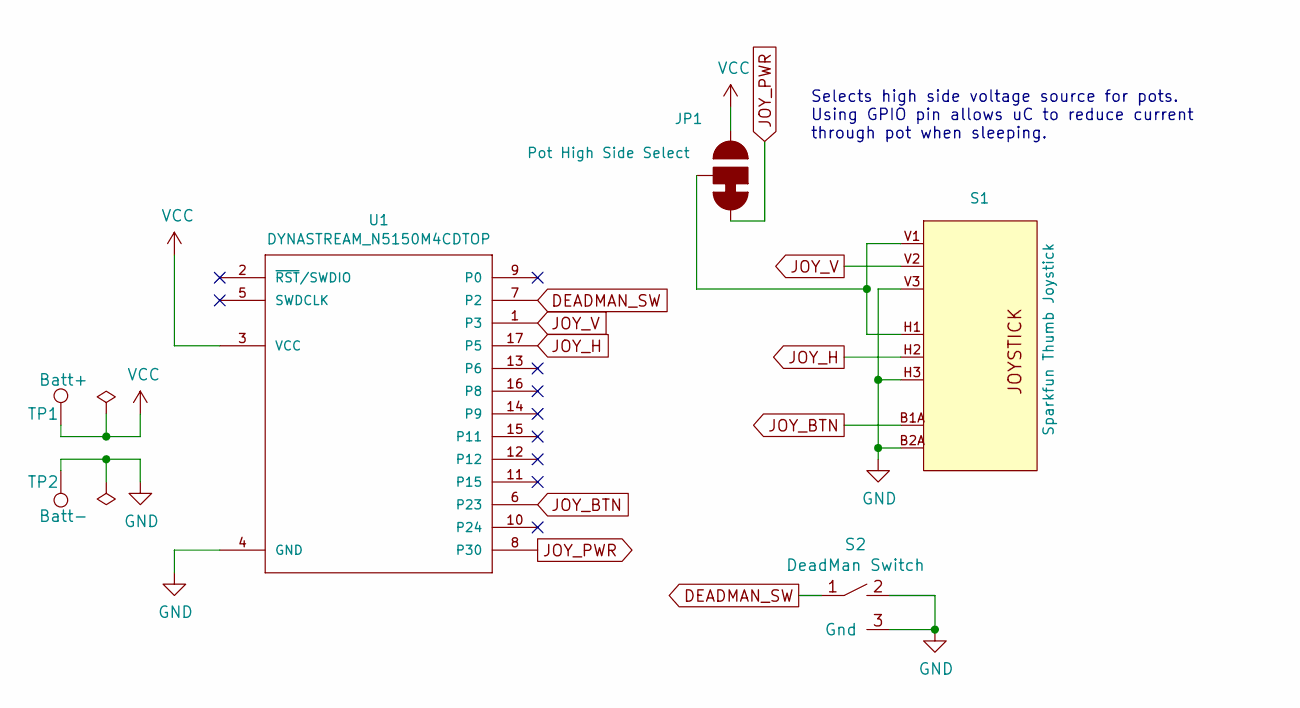
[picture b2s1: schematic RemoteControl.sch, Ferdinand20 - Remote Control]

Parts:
JP1: Pot High Side Select; SMT-JUMPER_3_1-NC_TRACE_SILK
S1: Sparkfun Thumb Joystick; JOYSTICK
S2: DeadMan Switch; PTS645V-SPST-RightAngleSwitch
TP1: Batt+; TestPoint_Pad_D2.0mm
TP2: Batt-; TestPoint_Pad_D2.0mm
U1: DYNASTREAM_N5150M4CDTOP; adam_custom-N5150M4CD_TOP

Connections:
DEADMAN_SW: S2.1, U1.7 (P2)
GND: S1.B2A (SEL-), S1.H3 (H-), S1.V3 (V-), S2.2, S2.3 (Gnd), TP2.1, U1.4 (GND)
JOY_BTN: S1.B1A (SEL+), U1.6 (P23)
JOY_H: S1.H2 (H), U1.17 (P5)
JOY_PWR: JP1.3, U1.8 (P30)
JOY_V: S1.V2 (V), U1.1 (P3)
unnamed: JP1.2, S1.H1 (H+), S1.V1 (V+)
VCC: JP1.1, TP1.1, U1.3 (VCC)

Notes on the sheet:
Selects high side voltage source for pots. Using GPIO pin allows uC to reduce current through pot when sleeping.

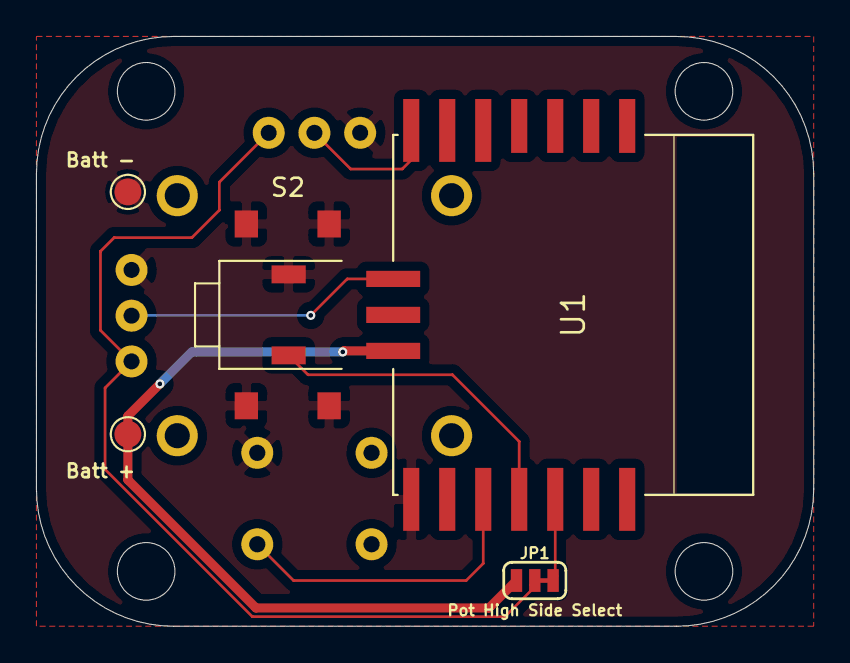
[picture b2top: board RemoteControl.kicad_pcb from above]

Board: 2 copper layers, 43.2 x 32.8 mm, 6 parts (1 on the bottom side), 8 nets.

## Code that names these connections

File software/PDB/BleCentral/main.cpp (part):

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    5                   TX_PIN_NUMBER       UART Transmit Output
    24                  MOTOR_RELAY_PIN     Relay Enable Output (Pulls ground down to Gnd via NPN transistor)
    15                  MANUAL_SWITCH_PIN   Manual Switch Input (Pulled low when user flips manual switch on)
    12                  LCD_SCK_PIN         LCD SPI Clock Output
    11                  LCD_MOSI_PIN        LCD SPI MOSI Output
    2                   LCD_TFTDC_PIN       LCD Data/Command Output
    8                   LCD_TFTCS_PIN       LCD SPI Chip Select Output
    23                  LCD_TFTRST_PIN      LCD Reset Output
    6 (AIN7)            BATTERY_VOLTAGE_PIN LiPo Battery Voltage Analog Input (via 300/600 ohm voltage divider)

   This sample is heavily influenced by Nordic's BLE UART Service Client (ble_app_uart_c) SDK sample.
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#define MANUAL_SWITCH_PIN       15

// The pins used to communicate with the LCD.
#define LCD_SCK_PIN             12
#define LCD_MOSI_PIN            11
#define LCD_TFTDC_PIN           2
#define LCD_TFTCS_PIN           8
#define LCD_TFTRST_PIN          23

// The analog input pin used to read the current LiPo battery voltage through 1/3 voltage divider.
#define BATTERY_VOLTAGE_PIN     NRF_ADC_CONFIG_INPUT_7  // P0.06 is AIN7 on nRF51422.
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APP_TIMER_DEF(g_batteryTimer);

// Objects used to control the LCD over SPI.
static Screen  g_screen(TICKS_PER_SECOND, LCD_MOSI_PIN, LCD_SCK_PIN, LCD_TFTCS_PIN, LCD_TFTDC_PIN, LCD_TFTRST_PIN);

// This global is set if the robot's LiPo battery drops below the minimum allowed voltage.
// Once set, the motors can no longer be enabled with the deadman switch without power cycling the PDB.
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
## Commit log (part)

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2019-07-07 July 6th Notes
    Initial commit about renewing my Robo-Magellan efforts.
2019-07-22 July 21st Notes
    Highlights:
    * Have received most of the parts to build Sawppy.
    * Just waiting for 3D printer and filament.
    * Completed BLE based debugging prototype and it looks pretty
    promising.
    * Researched new IMU sensors and picked a new one from Adafruit that I
2019-07-23 Advertise unique UUID from BLEMRI firmware
    Advertise a unique UUID for BLEMRI firmware so that the TCP/IP to BLE
    bridge program will only connect to BLEMRI devices and not just any
    device supporting Nordic's UART service.
2019-07-30 July 29th Notes
    My Prusa i3 MK3S arrived today.
2019-08-03 Allow BLEMRI to handle more than GDB packets
    Previously the BLEMRI firmware running on the nRF51 expected GDB remote
    packets to be sent so it would buffer data until it was full or the end
    of a packet was received. This commit removes that limitation. Now it
    buffers up the data until the buffer is full or no UART data has been
    sent from the LPC1768 for 1.5 serial frames. This fixes an issue where
    it failed to send the GDB remote protocol ack ('+') for the continue
2019-08-08 Add photo
2019-08-20 Add tests to exercise a new servo
    I just wanted a test that I could run on each of my 10 LX-16A servos to
    verify that they can all perform basic operations. These basic
    operations include:
    * Rotating to both extremes on command. Read position at end of
    each rotation to make sure that it reached desired location.
    * Rotating clockwise and counter-clockwise. Read the position as the
2019-10-05 Added PrusaSlicer print settings for Sawppy
    These are the custom Sawppy print settings that I have been using for
    printing its parts. I dialed in most of these settings when printing
    the wheels. On macOS, this file is added to the
    "~/Library/Application Support/PrusaSlicer/print" folder to make it
    available to the slicer.
2019-10-24 Add PrusaSlicer configs for latest parts
    * Differential parts
    * Body corners
    * 3mm nut clips
2019-10-30 October 29th notes
    Photo of the Sawppy build that I completed over the weekend.
2019-11-26 November 25th notes
    Highlights include:
    * Documented the creation of my custom wiring harness.
    * Updated overview to include the date of Robothon 2020 now that it
    has been set.
    * Update wire harness BOM to use the 10' length of ribbon cable instead
    of the 5'.
2020-01-25 Add twist demo to SawppyDrive test
    I used this to shoot my first video of Sawppy in action now that I have
    the intitial drive code working.
2020-02-03 Initial commit of BleJoystick firmware
    This is a basic proof of concept firmware for the handheld joystick/
    deadman switch hardware to be used with the Power Distribution Board
    (PDB). It will be updated in the future as I get closer to final
    hardware.
    The current features/limitations include:
    * I currently have it running on a micro:bit that I had onhand. This
2020-02-06 Initial PDB BleCentral prototype firmware
    This initial prototype runs on a nRF51 based micro:bit. At this point
    it can just wirelessly connect to BleJoystick devices via BLE and log
    the packets to the UART.
    There are still a few major things to be added to this prototype that
    will come in future commits:
    * OLED support for displaying updates of PDB/robot status.
2020-02-13 February 12th notes
    Highlights include:
    * Got BLE Central device code working enough to wirelessly connect to
    the joystick prototype.
    * Blocked on further PDB progress until I get a few parts that I have
    ordered from Adafruit and Sparkfun.
    * Reading a few books on behaviour based robot programming.
2020-02-20 February 20th notes
    I have received my Adafruit order.
2020-05-21 May 21st notes
2020-05-23 Reversed ST77XX_INVOFF & ST77XX_INVON
    Flipping these command values around made the invertDisplay() method
    work as expected. The original values match the ST7789 datasheet so it
    appears that the datasheet is probably the original source of this
    error.
2020-05-25 Update blemri firmware
    I used the new C structure initializer format with named struct fields
    for setting up the UART connection parameters to make it easier to
    read. I had used this format in some of my newer nRF51 code so I
    backported it to this project too.
    I also fixed a bug in its Makefile to pull the programming tools from
    the correct folder. I had already fixed the other nrfjprog
2020-07-06 Version 1 of Power Distribution Board
    This is my first KiCAD project, the Power Distribution Board for my
    RoboMagellan bot. This version was sent off to OSHPark for
    manufacturing on July 5th, 2020.
2020-07-06 Use correct template for PDB schematic
    I had moved my page layout description template to a different folder
    and forgot to update the schematic page layout to point to the new
    folder.
2020-07-12 Update link for 470pF cap
    My existing book of 0805 caps doesn't have a 470pF ceramic capacitor so
    I updated the link to point to the one from Digikey that I have
    ordered.
2020-07-21 Add BOM for Remote Control
2020-07-26 July 25th notes
    I finished soldering up the PDB PCB version 1 and tested it.
2020-08-01 Add line break to README
2020-08-04 ST7789 LCD driver cleanup
    There are some things that the ST7789 driver inherited from Adafruit
    precursors dealing with screen size and rotation that I don't like so
    I have modified this driver to correct them:
    * I don't like that a rotation of 0 actually asks the driver to invert
    the x and y axis when writing pixels while a rotation of 2 does no
    such inversions. Why isn't a rotation of 2, the default (0) rotation?
2020-08-04 Initial commit of RREFont library
    This is the library that I initially pulled down from @cbm80amiga 's
    GitHub repository in an attempt to speed up the 1.54" TFT display that
    I am currently using with the power distribution board. The GitHub link
    is:
    https://github.com/cbm80amiga/RREFont
    Later commits will come to make it build for the nRF51
2020-08-04 Update LiPo voltage levels
    I had previously used 1S voltage levels and not 2S. I also adjusted the
    cut-off voltage to 3.2V per cell instead of 3.0V since 3.0V is the
    absolute minimum that a LiPo cell should be allowed to discharge to and
    0.2V of margin is probably a good thing for battery life.
2020-08-05 Configure pins for better deep sleep support
    * Set deadman switch to be a sense input so that it can bring the CPU
    out of deep sleep.
    * Configure JOYSTICK_POWER_PIN to power pots when running and then set
    it low before going into deep sleep.
2020-08-09 Improve PDB serial receive code
    Now queue up the received packets into a circular buffer.
2020-08-09 August 9th notes
    I have the remote control working on final hardware and have been busy
    writing and improving firmware for the PDB and the remote control.
2020-08-10 Blink battery voltages when low
    I refactored the code to move the existing blink code out into its own
    Blinker helper class and then use it to make the battery voltages blink
    as well when they aren't green.
    I now calculate the elapsed time since the beginning of this blink
    cycle into Screen::update() where it is done once instead of for each
    indicator that is in the process of blinking.
2020-08-10 Move code out of PDB folder
    Pull remote control code and tests out of the PDB folder and just left
    the PDB code itself in that folder. This was done to have the software
    folder more closely resemble the hardware folder with respect to the
    PDB and RemoteControl subprojects.
2020-08-13 Can now drive robot with remote control
    * Use PdbSerial driver to get joystick state from PDB and use it to
    direct where the robot should drive instead of using stdin/stdout
    redirected from GDB as it did originally. This gets it working pretty
    much like Roger Cheng's original code.
    * I had to increase MAX_MISSED_BLE_PACKETS in the PDB firmware from 2
    to 30 as BLE packets are getting dropped if I get more than a few
2020-08-16 OpenSCAD design for the PDB enclosure
2020-08-22 August 21st notes
    Show some photos of my current remote control enclosure progress.
2020-08-30 Fix bumper thickness
    Had parameter to set it but I was hardcoding it to 1.0mm in
    ButtonBumper() module.
2020-09-13 Remove handle to top mounting screw
    There isn't enough room for the screw head.
2020-09-27 Update PDB back panel design
    It no longer slides in but has a single M3 screw that holds a plate
    inplace.
2021-03-23 March 23rd notes
    Back from taking a ~5 month break :)
2021-04-09 April 9th notes
    Documented the results of the BLE antenna experiments that I conducted.
2021-04-16 April 16th notes
    I have decided to try switching my IMU to use the newer sensor package
    that I bought from Adafruit back in 2019, when I started this project.
2021-04-19 Rewrite I2C drivers for new IMU sensors
    This is the first step in my switch over to the new NXP FXOS8700CQ
    accelerometer/magnetometer and FXAS21002C gyro sensors. I have
    implemented enough code to get raw sensors readings for calibrating.
    I still need to:
    * Not just hardcode the 100Hz sampling frequency as it is possible to
    run these new sensors up to 400Hz.
2021-04-21 Initial calibration data for my Adafruit Precision 9 DoF board
    files/config.ini contains the calibration values I have measured so far
    for the sensor.
    The .numbers and .csv files in the processing/calibration folder were
    used in calculating these calibration values.
2021-04-22 Sample sensors on FXOS8700CG data ready interrupt
    Previously I was using a 100Hz timer but the FXOS8700CG errata
    indicates that it is better to sample right after data is ready to
    reduce I2C traffic while magnetometer is being sampled.
2021-04-24 April 23rd notes
    Note about the port of my IMU Kalman filtering code to the Adafruit NXP
    9DoF Precision Breakout Board.
2021-05-19 Add virtual encoders and PID control to LX-16A servos
    This commit includes:
    * A simple program in the software/EncoderTest to test forward and
    reverse closed loop operation of the servos.
    * Copied over my PID library from the Ferdinand16 repository and made a
    few updates:
    * Now allow the sample time to be updated for each iteration and not
2021-06-01 Revert back to not waiting on BLE write response
    Improves the performance at the cost of higher liklihood of corrupt
    packets. I updated mriprog to better deal with these errors.
2021-06-05 SawppyDrive now uses closed loop control for LX-16A servos
    Changes include:
    * Now use LX16A_DriverMotor instead of LX16A_Servo for the 6 rolling
    servos controlled by the SawppyDrive class. These add the closed loop
    control for rotational speed.
    * Instead of using open loop power settings for controlling the 6
    drive servos, the percentage speed settings are used to set the
2021-06-07 Improve blemri throughput back to PC
    The code now queue up as many of the chunks directly to the BLE stack
    until it gets a BLE_ERROR_NO_TX_PACKETS error. Once that error is
    received, the packets are placed in the chunk queue which drains as the
    BLE stack completes the sending of previous chunks. Once this queue is
    drained, the code will go back to submitting directly to the BLE stack
    again.

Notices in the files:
software/PDB/BleCentral/main.cpp:
Copyright (C) 2020  Adam Green (https://github.com/adamgreen)
modify it under the terms of the GNU General Public License
hardware/PDB/PDB.kicad_pcb:
Released under the Creative Commons Attribution Share-Alike 4.0 License
hardware/PDB/PDB.sch:
https://creativecommons.org/licenses/by-sa/4.0
